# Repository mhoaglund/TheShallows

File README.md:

# TheShallows
Submission collection site for AOV 2018 project

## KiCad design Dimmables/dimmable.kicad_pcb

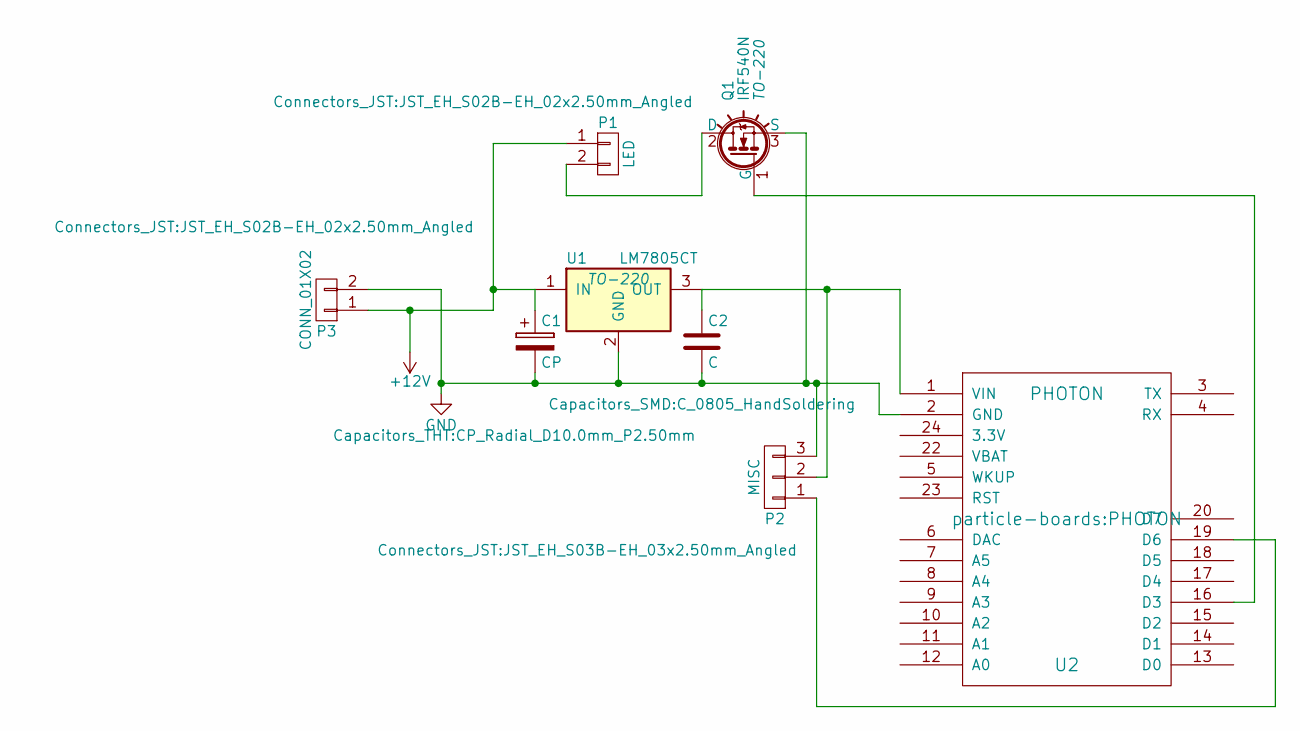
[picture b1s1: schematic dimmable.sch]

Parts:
C1: CP; CP_Radial_D10.0mm_P2.50mm
C2: C; C_0805_HandSoldering
P1: LED; JST_EH_S02B-EH_02x2.50mm_Angled
P2: MISC; JST_EH_S03B-EH_03x2.50mm_Angled
P3: CONN_01X02; JST_EH_S02B-EH_02x2.50mm_Angled
Q1: IRF540N; TO-220
U1: LM7805CT; TO-220
U2: PHOTON

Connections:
+12V: C1.1, P1.1, P3.1, U1.1 (IN)
GND: C1.2, C2.2, P2.3, P3.2, Q1.3 (S), U1.2 (GND), U2.2 (GND)
unnamed: C2.1, P2.2, U1.3 (OUT), U2.1 (VIN)
unnamed: P1.2, Q1.2 (D)
unnamed: P2.1, U2.19 (D6)
unnamed: Q1.1 (G), U2.16 (D3)

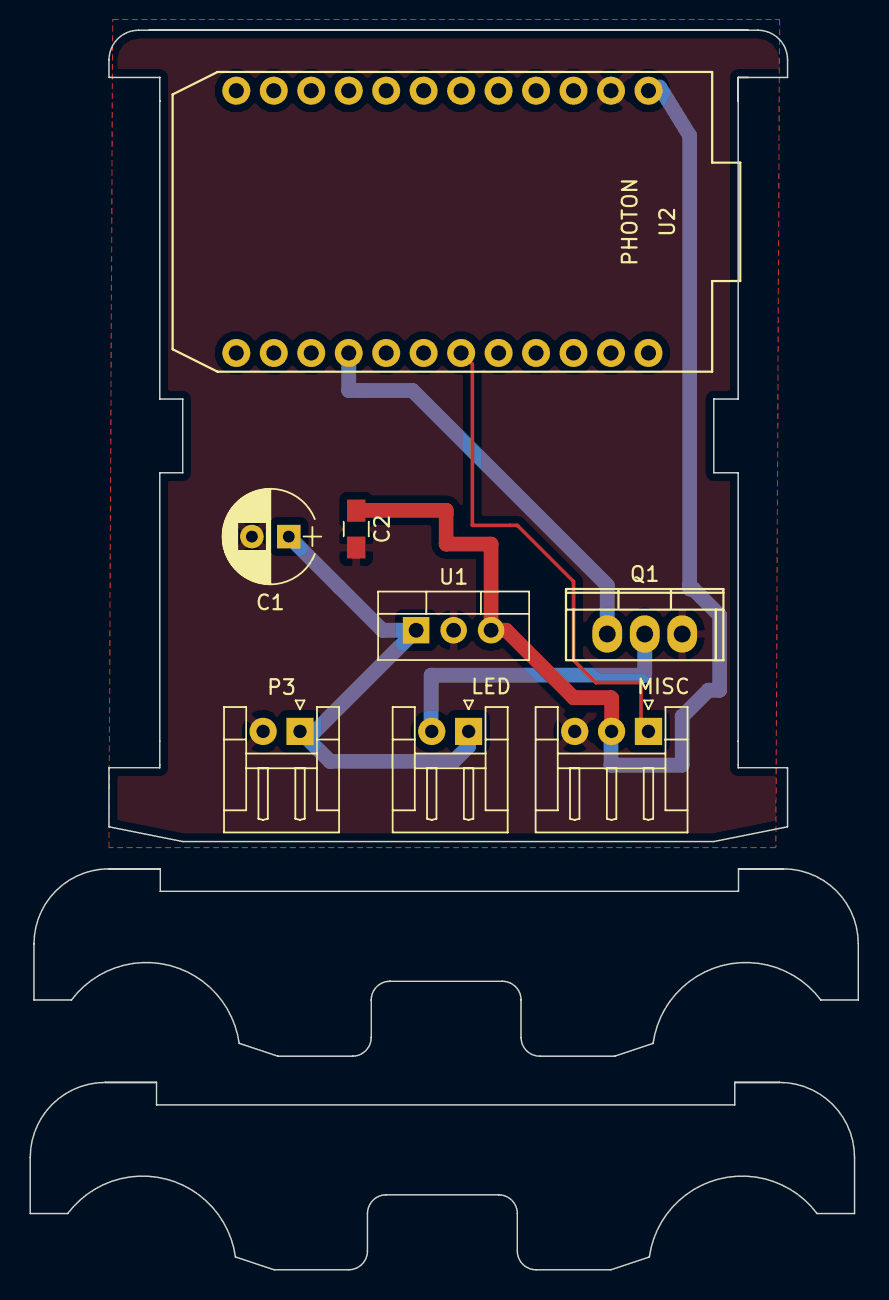
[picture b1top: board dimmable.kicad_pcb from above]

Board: 2 copper layers, 56.1 x 84.0 mm, 8 parts (0 on the bottom side), 6 nets.

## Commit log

2017-07-01 raw express project
2017-07-01 just some stubs for now
2017-07-02 boilerplate
2017-07-02 added moment and uuid
2017-07-03 blurg jquery menu whatever
2017-07-03 derping along
2017-07-03 more dumb front end stuff
2017-08-01 stub city
2017-08-01 dropping in more opencv stubs
2017-08-01 more blurgy copypasta
2017-08-03 more chunky stuff
2017-08-04 some renaming and moving stuff around
2017-08-04 just a docstring
2017-08-04 more chunkers
2017-08-07 tweaks and dhcpd
2017-08-07 added a new reservation
2017-08-07 corrected ip
2017-08-07 python
2017-08-07 tweaks!
2017-08-07 yep yep yep
2017-08-07 more foundational stuff
2017-08-16 more delay
2017-08-16 more tweaks
2017-08-16 moving view from input thread to output
2017-08-16 weird
2017-08-16 still poking away at this fullscreen stuff
2017-08-16 watchdog and ROI stuff
2017-08-16 Tweaks from device
2017-08-16 cleanup
2017-08-23 added pcb draft
2017-08-25 new routing
2017-09-14 blah blah
2017-09-30 tweaks after proto 1
2017-09-30 updated pcbs
2017-10-01 resistors for indicator lights
2017-10-01 adding list page and dust stuff
2017-10-06 basic order template in place
2017-10-06 more boring front end stuff
2017-10-09 glossary stuff
2017-10-14 pitch deck
2017-10-14 scroll wheel firmware
2017-10-27 interaction refinement
2017-10-27 minor stuff
2017-10-28 new gradient for every timestamp
2017-10-28 continuing to tweak
2017-10-28 fleshing out display stuff further, still needs tweaks
2017-10-28 more tweaks, half-open state experiments
2017-10-28 more shit
2017-10-29 functional visible-element determination
2017-10-29 just snippets
2017-10-29 initial wonky scrollopen stuff
2017-11-08 ibm plex, restyle
2017-11-08 arrow thing, span for rules
2017-11-09 some tweaks
2017-11-09 new approach to ui
2017-11-15 state stuff, spacing for change order list
2017-11-17 DXFs for plate components
2017-11-27 latest dxfs for plate jacket components
2017-11-27 stubs
2017-11-27 underscore and client side data access stub
2017-12-04 mouse wheel stuff that I apparently didn't check in when I wrote it
2017-12-05 scroll smoothing, stubs, upload page
2017-12-07 tidying query
2017-12-13 just what it looks like
2017-12-20 copypasta and annotated dxfs for machining
2017-12-21 stubs and workshop sheet draft
2017-12-27 workshop updates, bash script for jetson
2018-01-01 drag and drop stuff
2018-01-01 more stubs
2018-01-03 object stuff
2018-01-04 object template and other crap
2018-01-04 blurging through client side stuff
2018-01-05 uuuughhhh
2018-01-05 canned photos, better interaction, better data
2018-01-06 vector move recording
2018-01-06 hmmm
2018-01-06 just some beginner shit
2018-01-06 starting on the intro stuff
2018-01-06 intro stuff, incomplete
2018-01-06 junk removal, some responsive stuff
2018-01-06 addtl small responsive details
2018-01-06 detail dust template, small tweaks
2018-01-06 detail raising and clearing
2018-01-07 small additions to detail scenario
2018-01-07 username storage, visual cleanup
2018-01-07 cleanup and rerun intro functionality
2018-01-07 added unique shade effect for new users
2018-01-08 figured out box sizing for the grid for real this time, added submit button
2018-01-11 js vector and marker placement
2018-01-11 removed css animation for now
2018-01-11 wheel firmware corrections
2018-01-14 submission stuff
2018-01-14 loading stuff
2018-01-14 refreshing at the top stuff
2018-01-14 simplified data
2018-01-14 catching back up
2018-01-16 success stubs
2018-01-17 stubs and touch punch
2018-01-17 just some front end shit
2018-01-17 some submit button stuff
2018-01-17 visual tweaks
2018-02-22 moved kiosk / document management stuff over
2018-02-24 stubs for scan naming and uploading
2018-03-03 latest workshop
2018-03-09 server bindings, improvements, automated doc workflow
2018-03-09 proved out automated workflow stuff
2018-03-09 whewps
2018-03-09 automated scan and upload workflow
2018-03-09 small refinements, adding graphical cues
2018-03-09 crappy serial number stuff for short term
2018-03-09 changed reprint prompt structure
2018-03-09 tweaks for mobile, updated form
2018-03-10 back to whatever
2018-03-10 updated form and field binding
2018-03-14 some dropped in changes from another repo, css updates, addendum integration, performance improvements
2018-03-14 small tweaks, removing third localization
2018-03-26 technical drawings and dxfs
2018-04-05 improvements to upload interface, some messy css stuff
2018-04-06 added intro page
2018-07-13 screen tests in the firmware, tablet dimensions for case
2018-07-13 wifi dimmer board
2018-07-15 production files for wifi dimmer, visual changes
2018-07-15 more visual stuff
2018-07-16 form improvements
2018-07-25 visual fixes, attempted performance fixes
2018-07-25 more styling changes
2018-08-02 optimized the absolute shit out of the repaint
2018-08-09 tweak city, some bug fixes
2018-08-09 cleanup, re-familiarization, QOL parameterization in docmanager
2018-09-15 restructured form
2018-09-15 updated server binding
2018-09-22 new html pdf generator routine to replace the cantankerous old native code version
2018-09-22 dubious improvements
2018-09-22 end to end testing of new pdf process, still needs cleanup
2018-09-24 button press for wheel firmware, and some other crap kicad whipped up
2018-09-24 got intro written
2018-09-24 pretty cool commit here
2018-09-29 minor tweaks
2018-09-29 starting to optimize and remove extra stuff
2018-09-29 image link tweak
2018-09-30 optimization, rework of grid, etc.
2018-09-30 dealing with keyboard bump on mobile
2018-09-30 tiny edits, unhooked formatting logic from kiosk app
2018-10-02 stubbed out hotkey setup in wheel firmware
2018-10-02 firmware tweaks, css tweaks
2018-10-02 moved some font statements around
2018-10-02 added nicescroll to intro for projector table control
2018-10-03 added clutch to restore polling interval
2018-10-03 tweaks from kiosk
2018-10-03 tweaked wheel firmware, restored batch file, removed an old package
2018-10-03 removed some crap
2018-10-04 tentative package update
2018-10-04 moved css around, redid listview to match other assets and project better
2018-10-04 matching case for a variable, this is a great commit
2018-10-04 layout et al
2018-10-04 case
2018-10-04 form tweaks
2018-10-05 form updates, polling interval, hopeful puppeteer fix
2018-10-05 css and kiosk app stuff
2018-10-05 completing the path normalization work
2018-10-05 local record caching
2018-10-05 keypress listeners
2018-10-05 derp
2018-10-05 fixes from embedded system
2018-10-12 some dumb js stuff, and an actual firmware solution
2018-10-18 cleanup of tablet site
2018-10-18 visual tweaks from week 1
2018-10-18 visual tweaks for upload
2018-10-18 template impro
2018-10-18 added redundancy management for overwrites, improved ui, added refresh button
2018-10-20 tweaked fillable form, refactored move recording system, added underscore
2018-10-21 sending an empty variable back was a good call
